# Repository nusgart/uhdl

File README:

MIT CADR HDL --- Verilog FPGA implementation of the MIT CADR

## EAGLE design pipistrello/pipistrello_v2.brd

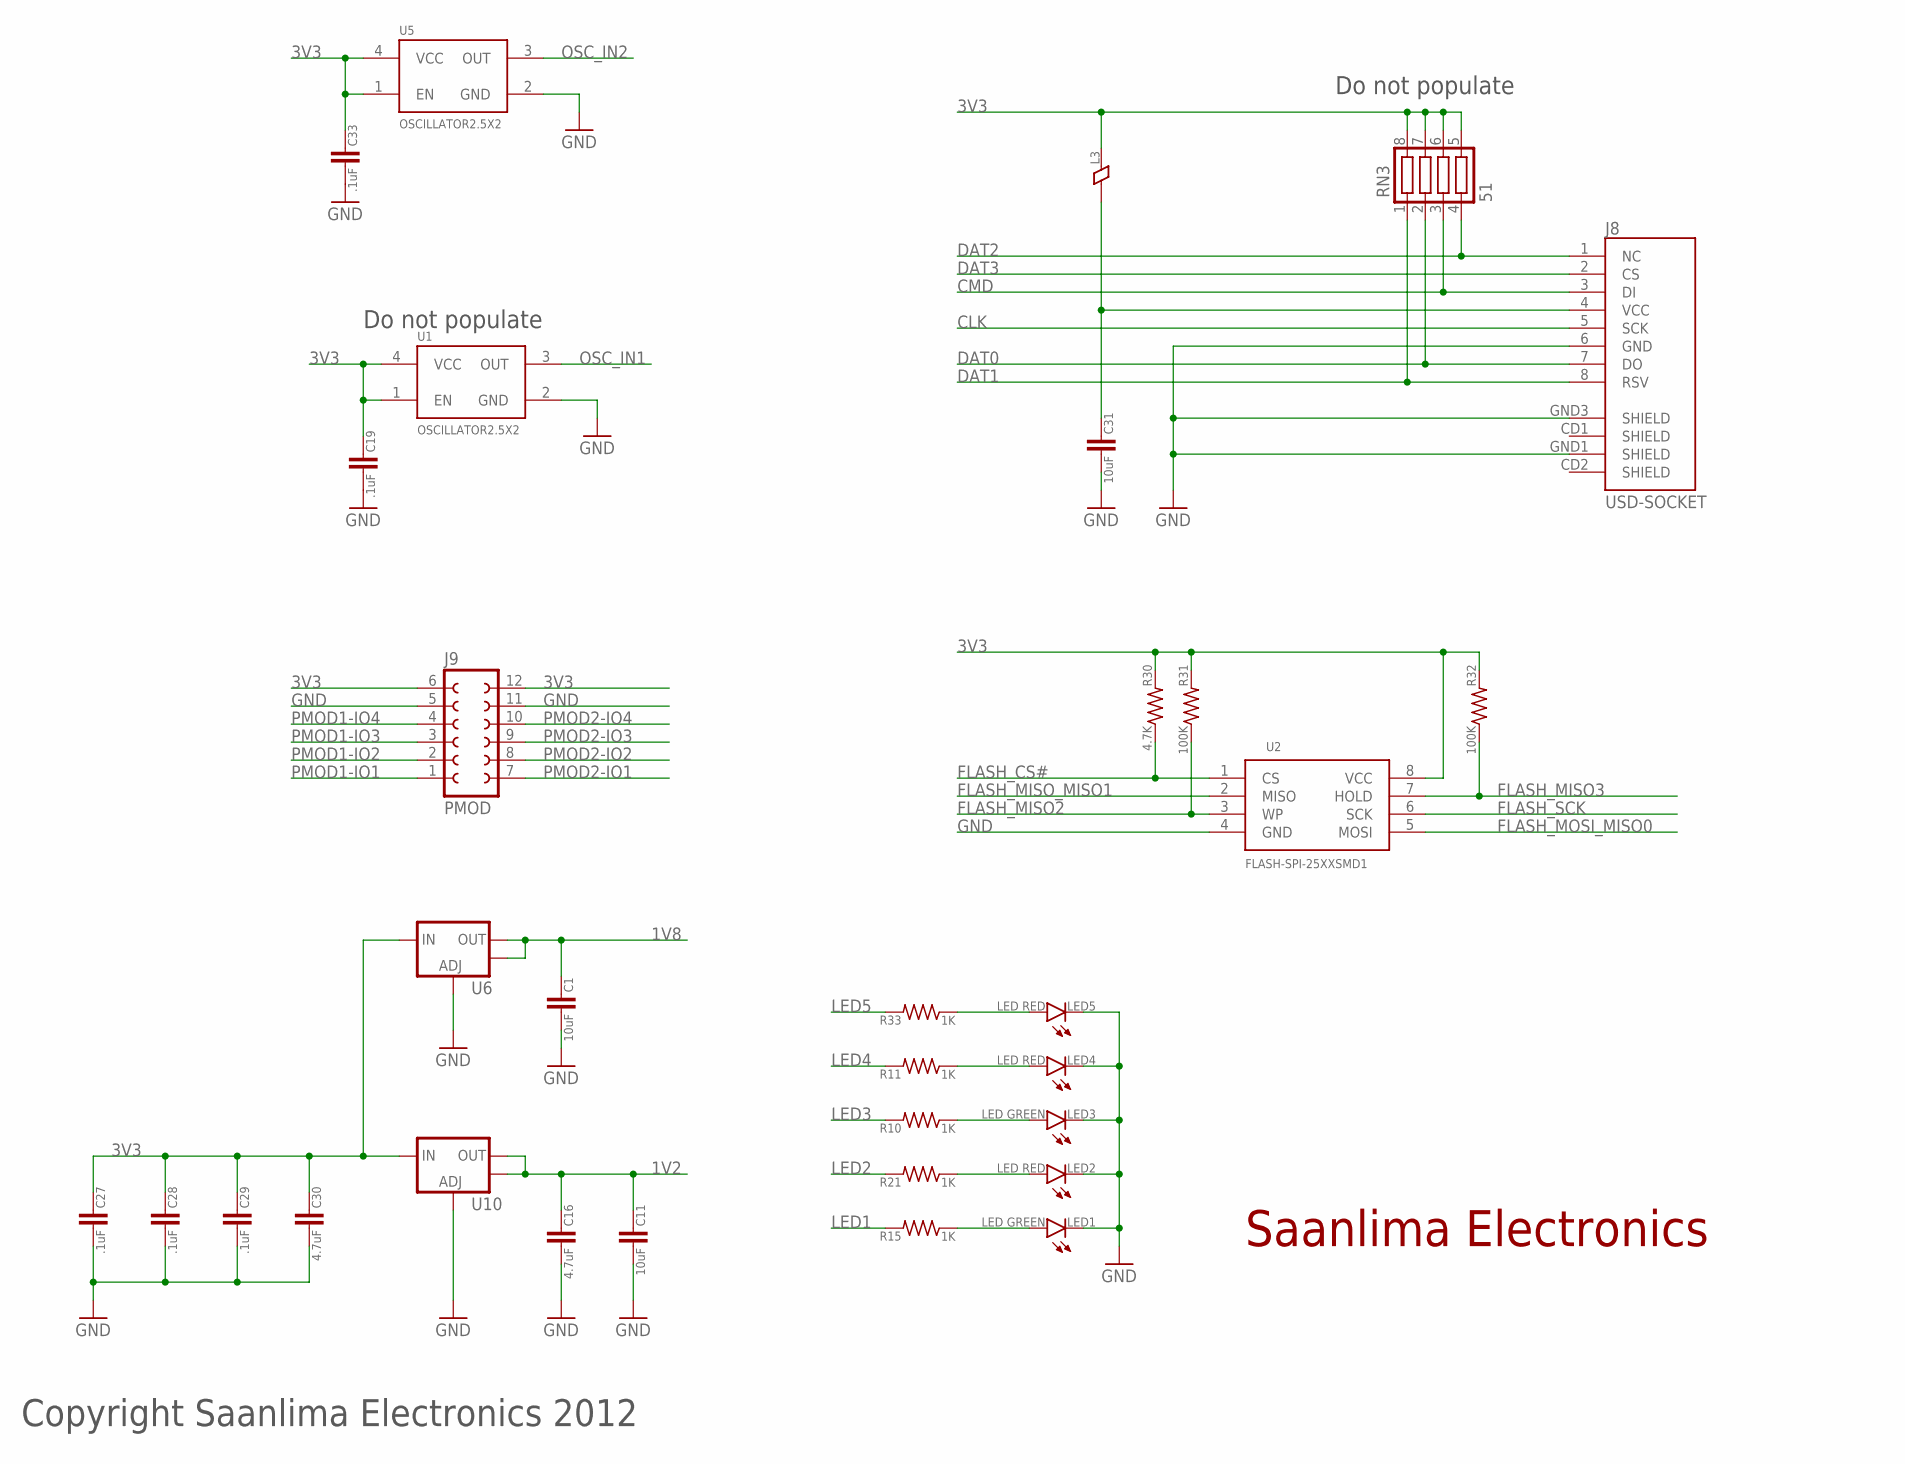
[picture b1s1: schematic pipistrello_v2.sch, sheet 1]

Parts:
C1, C11: 10uF; 0805
C16, C30: 4.7uF; 0402
C19, C27, C28, C29, C33: .1uF; 0402
C31: 10uF; 0603
J8: USD-SOCKET; MICRO-SD-SOCKET-PP
J9: PMOD
L3: FERRITE0402; 0402
LED1, LED3: LED GREEN; 0805_POL
LED2, LED4, LED5: LED RED; 0805_POL
R10, R11, R15, R21, R33: 1K; 0402
R30: 4.7K; 0402
R31, R32: 100K; 0402
RN3: 51; CTS742C083
U1, U5: OSCILLATOR2.5X2; CRYSTAL-OSC-SMD-2.5X2
U2: FLASH-SPI-25XXSMD1; SO08-EIAJ
U6, U10: V_REG_LM1117SOT223; SOT223

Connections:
1V2: C11.1, C16.1, U10.2 (OUT), U10.4 (OUT); also elsewhere on the board
1V8: C1.1, U6.2 (OUT), U6.4 (OUT); also elsewhere on the board
3V3: C19.1, C27.1, C28.1, C29.1, C30.1, C33.1, J9.6, J9.12, L3.2, R30.2, R31.2, R32.2, RN3.5, RN3.6, RN3.7, RN3.8, U1.1 (EN), U1.4 (VCC), U2.8 (VCC), U5.1 (EN), U5.4 (VCC), U6.3 (IN), U10.3 (IN); also elsewhere on the board
CLK: J8.5 (SCK); also elsewhere on the board
CMD: J8.3 (DI), RN3.3; also elsewhere on the board
DAT0: J8.7 (DO), RN3.2; also elsewhere on the board
DAT1: J8.8 (RSV), RN3.1; also elsewhere on the board
DAT2: J8.1 (NC), RN3.4; also elsewhere on the board
DAT3: J8.2 (CS); also elsewhere on the board
FLASH_CS#: R30.1, U2.1 (CS); also elsewhere on the board
FLASH_MISO2: R31.1, U2.3 (WP); also elsewhere on the board
FLASH_MISO3: R32.1, U2.7 (HOLD); also elsewhere on the board
FLASH_MISO_MISO1: U2.2 (MISO); also elsewhere on the board
FLASH_MOSI_MISO0: U2.5 (MOSI); also elsewhere on the board
FLASH_SCK: U2.6 (SCK); also elsewhere on the board
GND: C1.2, C11.2, C16.2, C19.2, C27.2, C28.2, C29.2, C30.2, C31.2, C33.2, J8.6 (GND), J8.GND1 (SHIELD), J8.GND3 (SHIELD), J9.5, J9.11, LED1.- (C), LED2.- (C), LED3.- (C), LED4.- (C), LED5.- (C), U1.2 (GND), U2.4 (GND), U5.2 (GND), U6.1 (ADJ), U10.1 (ADJ); also elsewhere on the board
LED1: R15.2; also elsewhere on the board
LED2: R21.2; also elsewhere on the board
LED3: R10.2; also elsewhere on the board
LED4: R11.2; also elsewhere on the board
LED5: R33.2; also elsewhere on the board
unnamed: LED2.+ (A), R21.1
unnamed: LED3.+ (A), R10.1
unnamed: C31.1, J8.4 (VCC), L3.1
unnamed: LED1.+ (A), R15.1
unnamed: LED4.+ (A), R11.1
unnamed: LED5.+ (A), R33.1
OSC_IN1: U1.3 (OUT); also elsewhere on the board
OSC_IN2: U5.3 (OUT); also elsewhere on the board
PMOD1-IO1: J9.1; also elsewhere on the board
PMOD1-IO2: J9.2; also elsewhere on the board
PMOD1-IO3: J9.3; also elsewhere on the board
PMOD1-IO4: J9.4; also elsewhere on the board
PMOD2-IO1: J9.7; also elsewhere on the board
PMOD2-IO2: J9.8; also elsewhere on the board
PMOD2-IO3: J9.9; also elsewhere on the board
PMOD2-IO4: J9.10; also elsewhere on the board

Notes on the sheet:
Saanlima Electronics
Copyright Saanlima Electronics 2012
Do not populate

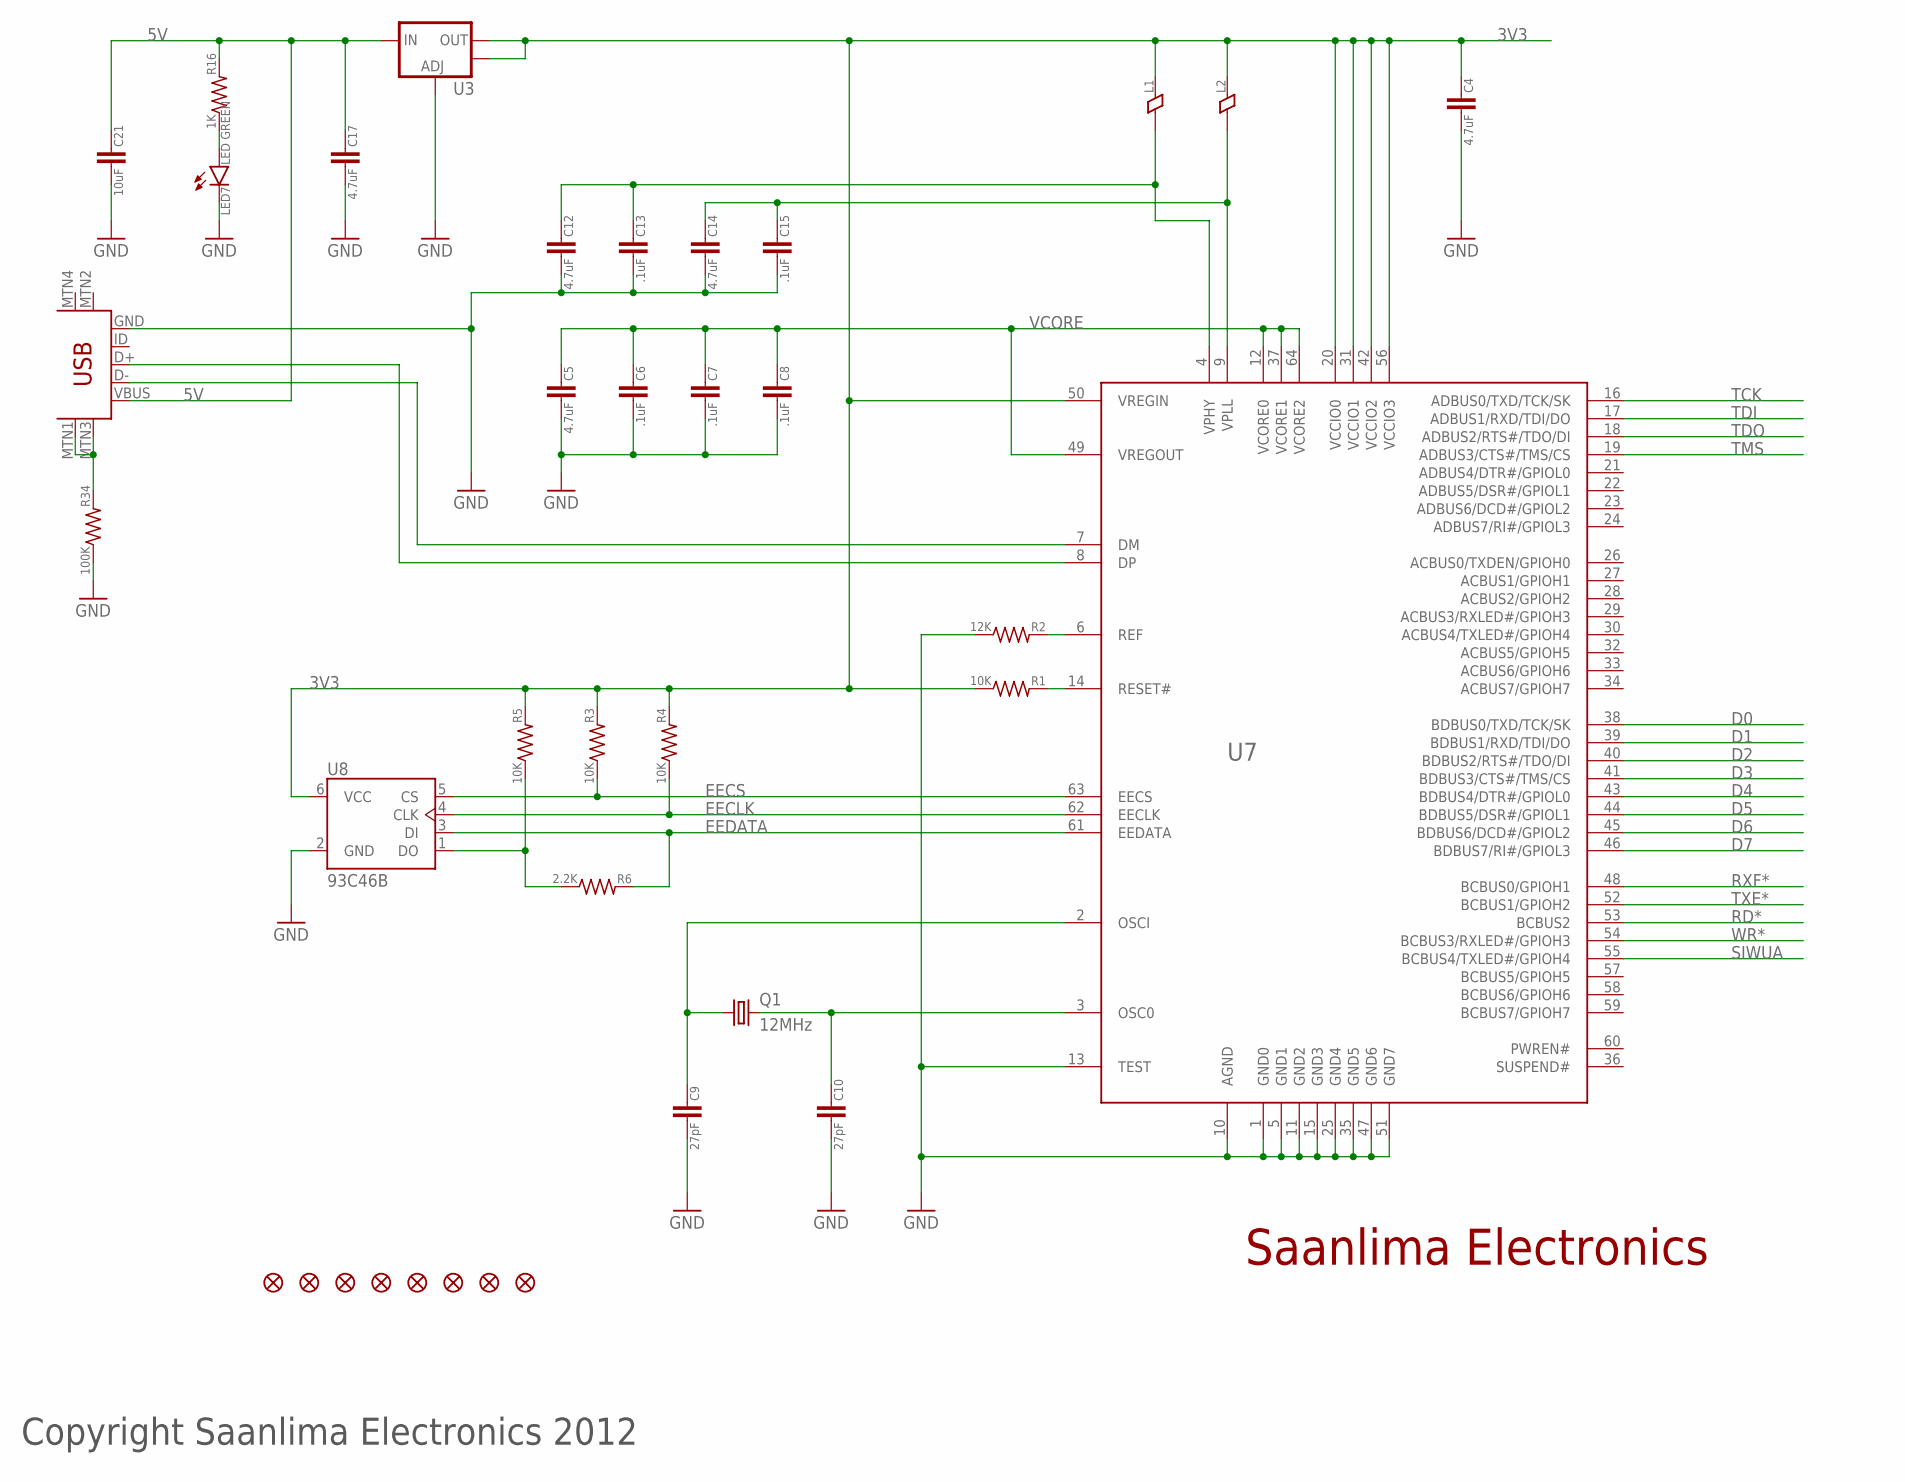
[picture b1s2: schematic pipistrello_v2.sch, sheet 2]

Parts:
C4, C5, C12, C14, C17: 4.7uF; 0402
C6, C7, C8, C13, C15: .1uF; 0402
C9, C10: 27pF; 0402
C21: 10uF; 0603
J7: USB-MINIB-5PIN; USB-MINIB
JP1, JP2, JP3, JP4, JP5, JP6, JP7, JP8: FIDUCIAL1X2; FIDUCIAL-1X2
L1, L2: FERRITE0402; 0402
LED7: LED GREEN; 0805_POL
Q1: 12MHz; CRYSTAL3.2X2.5MM
R1, R3, R4, R5: 10K; 0402
R2: 12K; 0402
R6: 2.2K; 0402
R16: 1K; 0402
R34: 100K; 0402
U3: V_REG_LM1117SOT223; SOT223
U7: FT2232H; LQFP64
U8: 93C46B; SOT23-6

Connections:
3V3: C4.1, L1.2, L2.2, R1.1, R3.2, R4.2, R5.2, U3.2 (OUT), U3.4 (OUT), U7.20 (VCCIO0), U7.31 (VCCIO1), U7.42 (VCCIO2), U7.50 (VREGIN), U7.56 (VCCIO3), U8.6 (VCC); also elsewhere on the board
5V: C17.1, C21.1, J7.VBUS, R16.2, U3.3 (IN); also elsewhere on the board
D0: U7.38 (BDBUS0/TXD/TCK/SK); also elsewhere on the board
D1: U7.39 (BDBUS1/RXD/TDI/DO); also elsewhere on the board
D2: U7.40 (BDBUS2/RTS#/TDO/DI); also elsewhere on the board
D3: U7.41 (BDBUS3/CTS#/TMS/CS); also elsewhere on the board
D4: U7.43 (BDBUS4/DTR#/GPIOL0); also elsewhere on the board
D5: U7.44 (BDBUS5/DSR#/GPIOL1); also elsewhere on the board
D6: U7.45 (BDBUS6/DCD#/GPIOL2); also elsewhere on the board
D7: U7.46 (BDBUS7/RI#/GPIOL3); also elsewhere on the board
EECLK: R4.1, U7.62 (EECLK), U8.4 (CLK)
EECS: R3.1, U7.63 (EECS), U8.5 (CS)
EEDATA: R6.2, U7.61 (EEDATA), U8.3 (DI)
GND: C4.2, C5.2, C6.2, C7.2, C8.2, C9.2, C10.2, C12.2, C13.2, C14.2, C15.2, C17.2, C21.2, J7.GND, LED7.- (C), R2.1, R34.1, U3.1 (ADJ), U7.1 (GND0), U7.5 (GND1), U7.10 (AGND), U7.11 (GND2), U7.13 (TEST), U7.15 (GND3), U7.25 (GND4), U7.35 (GND5), U7.47 (GND6), U7.51 (GND7), U8.2 (GND); also elsewhere on the board
unnamed: J7.MTN1 (MTN2), J7.MTN3 (MTN1), R34.2
unnamed: C9.1, Q1.1, U7.2 (OSCI)
unnamed: C10.1, Q1.3 (2), U7.3 (OSC0)
unnamed: LED7.+ (A), R16.1
unnamed: J7.D-, U7.7 (DM)
unnamed: J7.D+, U7.8 (DP)
unnamed: C14.1, C15.1, L2.1, U7.9 (VPLL)
unnamed: R1.2, U7.14 (RESET#)
unnamed: R2.2, U7.6 (REF)
unnamed: C12.1, C13.1, L1.1, U7.4 (VPHY)
unnamed: R5.1, R6.1, U8.1 (DO)
RD*: U7.53 (BCBUS2); also elsewhere on the board
RXF*: U7.48 (BCBUS0/GPIOH1); also elsewhere on the board
SIWUA: U7.55 (BCBUS4/TXLED#/GPIOH4); also elsewhere on the board
TCK: U7.16 (ADBUS0/TXD/TCK/SK); also elsewhere on the board
TDI: U7.17 (ADBUS1/RXD/TDI/DO); also elsewhere on the board
TDO: U7.18 (ADBUS2/RTS#/TDO/DI); also elsewhere on the board
TMS: U7.19 (ADBUS3/CTS#/TMS/CS); also elsewhere on the board
TXE*: U7.52 (BCBUS1/GPIOH2); also elsewhere on the board
VCORE: C5.1, C6.1, C7.1, C8.1, U7.12 (VCORE0), U7.37 (VCORE1), U7.49 (VREGOUT), U7.64 (VCORE2)
WR*: U7.54 (BCBUS3/RXLED#/GPIOH3); also elsewhere on the board

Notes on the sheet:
Saanlima Electronics
Copyright Saanlima Electronics 2012

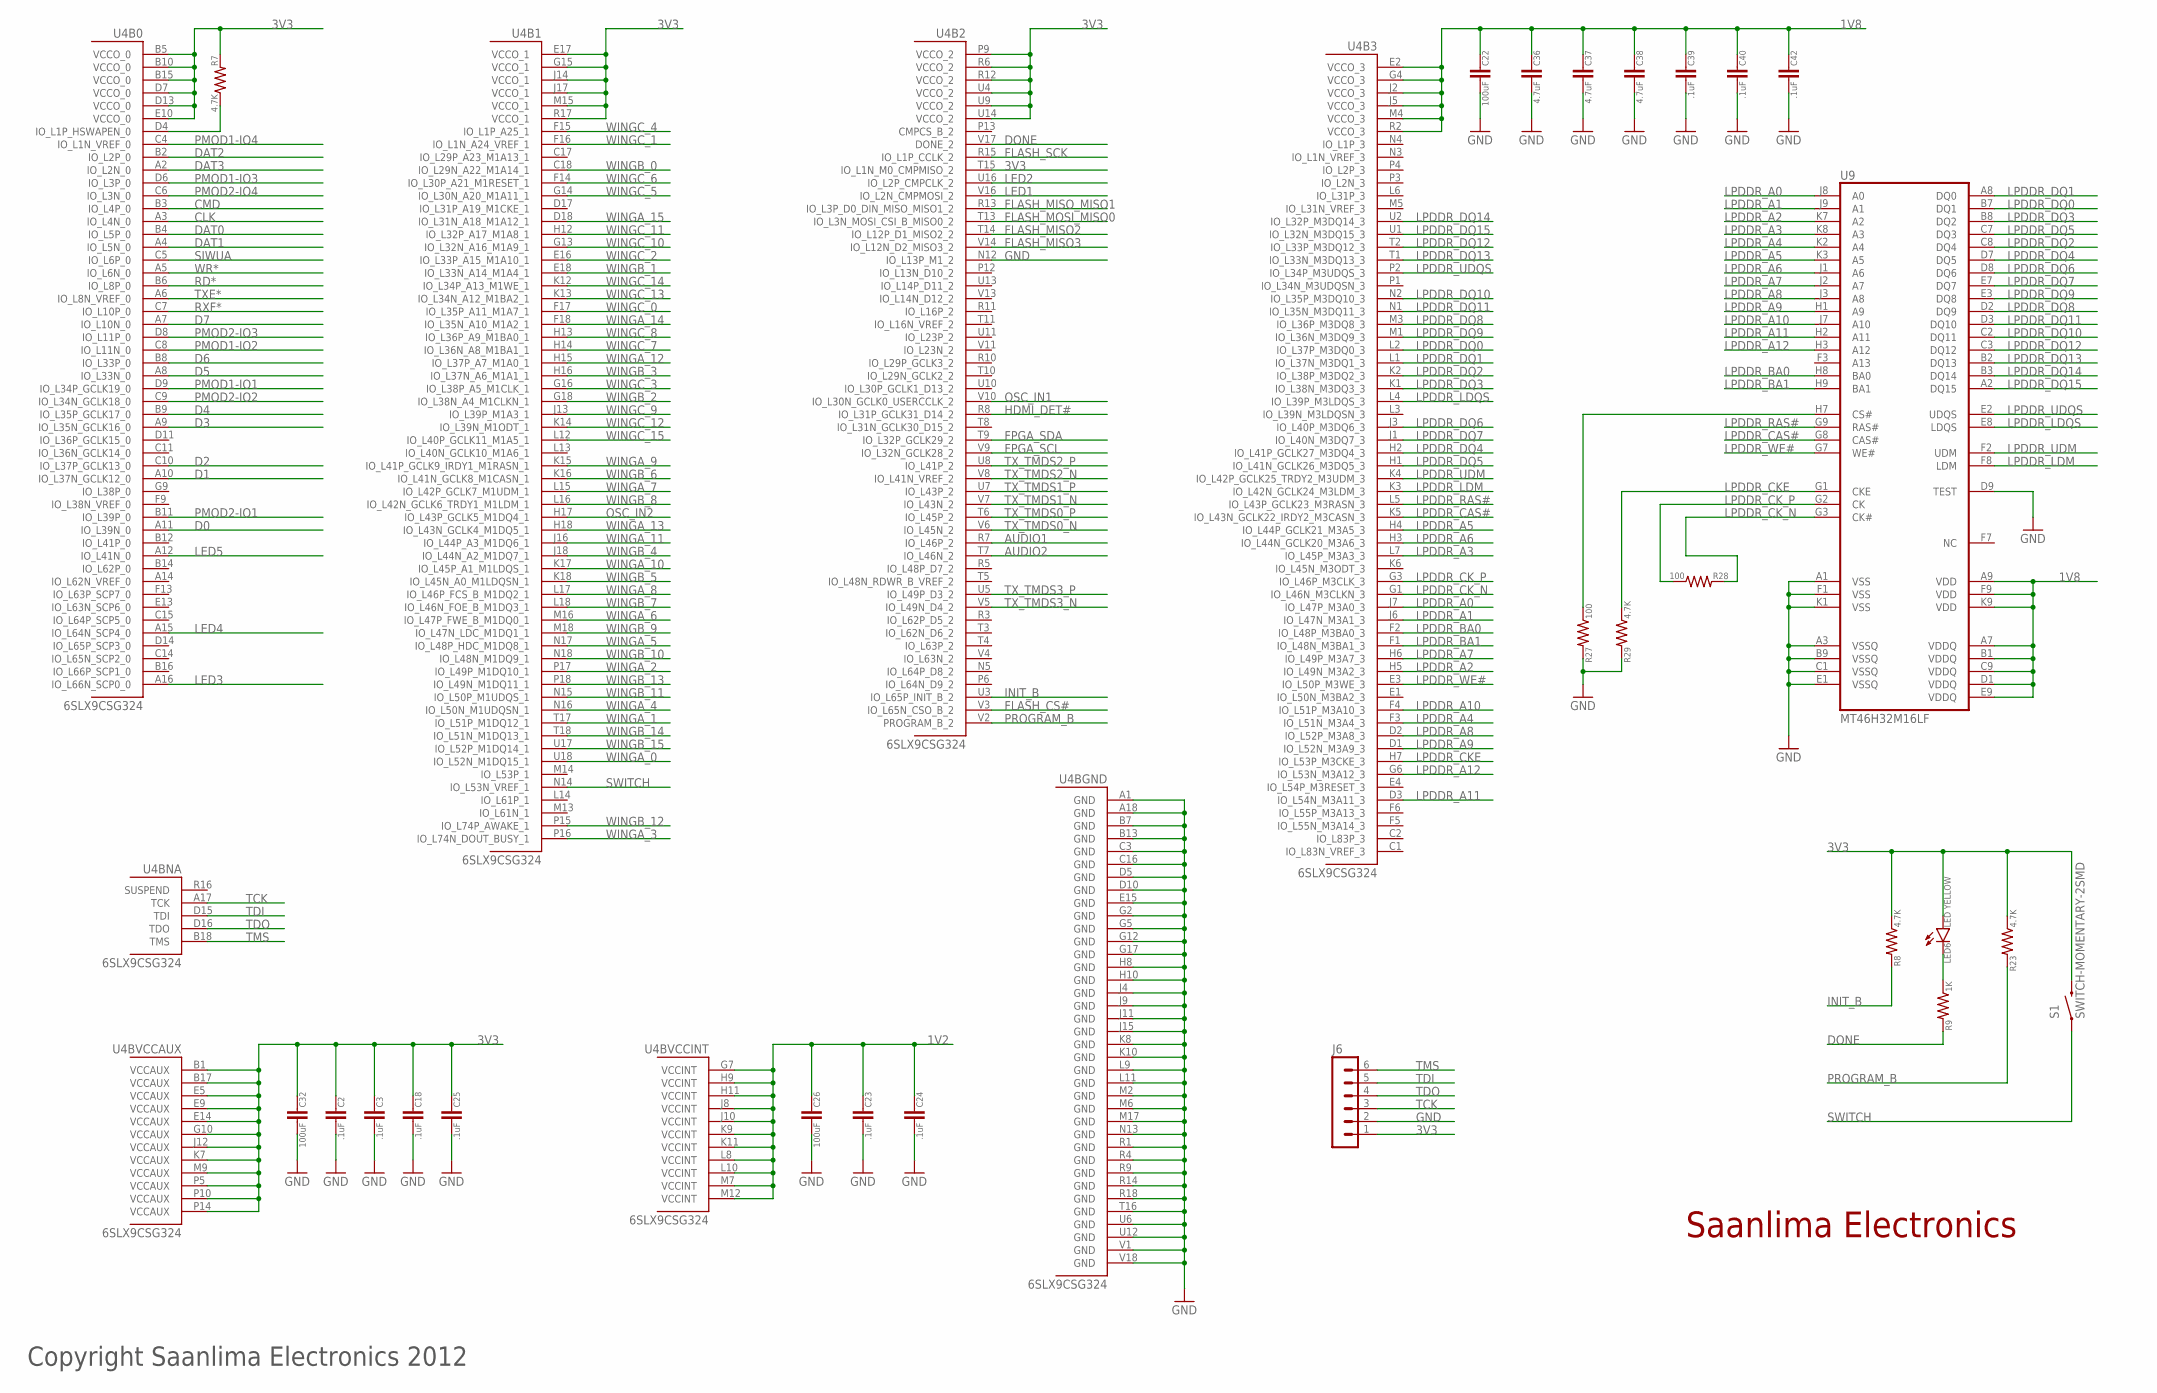
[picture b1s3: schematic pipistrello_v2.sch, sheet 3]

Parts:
C2, C3, C18, C23, C24, C25, C39, C40, C42: .1uF; 0402
C22, C26, C32: 100uF; 1206
C36, C37, C38: 4.7uF; 0402
J6: MA06-1
LED6: LED YELLOW; 0805_POL
R7, R8, R23, R29: 4.7K; 0402
R9: 1K; 0402
R27, R28: 100; 0402
S1: SWITCH-MOMENTARY-2SMD; TACTILE_SWITCH_SMD
U4: 6SLX9CSG324; CS324
U9: MT46H32M16LF; FBFA60-6X10

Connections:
1V2: C23.1, C24.1, C26.1, U4.G7 (VCCINT), U4.H9 (VCCINT), U4.H11 (VCCINT), U4.J8 (VCCINT), U4.J10 (VCCINT), U4.K9 (VCCINT), U4.K11 (VCCINT), U4.L8 (VCCINT), U4.L10 (VCCINT), U4.M7 (VCCINT), U4.M12 (VCCINT); also elsewhere on the board
1V8: C22.1, C36.1, C37.1, C38.1, C39.1, C40.1, C42.1, U4.E2 (VCCO_3), U4.G4 (VCCO_3), U4.J2 (VCCO_3), U4.J5 (VCCO_3), U4.M4 (VCCO_3), U4.R2 (VCCO_3), U9.A7 (VDDQ), U9.A9 (VDD), U9.B1 (VDDQ), U9.C9 (VDDQ), U9.D1 (VDDQ), U9.E9 (VDDQ), U9.F9 (VDD), U9.K9 (VDD); also elsewhere on the board
3V3: C2.1, C3.1, C18.1, C25.1, C32.1, J6.1, LED6.+ (A), R7.2, R8.1, R23.1, S1.3 (2), U4.B1 (VCCAUX), U4.B5 (VCCO_0), U4.B10 (VCCO_0), U4.B15 (VCCO_0), U4.B17 (VCCAUX), U4.D7 (VCCO_0), U4.D13 (VCCO_0), U4.E5 (VCCAUX), U4.E9 (VCCAUX), U4.E10 (VCCO_0), U4.E14 (VCCAUX), U4.E17 (VCCO_1), U4.G10 (VCCAUX), U4.G15 (VCCO_1), U4.J12 (VCCAUX), U4.J14 (VCCO_1), U4.J17 (VCCO_1), U4.K7 (VCCAUX), U4.M9 (VCCAUX), U4.M15 (VCCO_1), U4.P5 (VCCAUX), U4.P9 (VCCO_2), U4.P10 (VCCAUX), U4.P14 (VCCAUX), U4.R6 (VCCO_2), U4.R12 (VCCO_2), U4.R17 (VCCO_1), U4.T15 (IO_L1N_M0_CMPMISO_2), U4.U4 (VCCO_2), U4.U9 (VCCO_2), U4.U14 (VCCO_2); also elsewhere on the board
AUDIO1: U4.R7 (IO_L46P_2); also elsewhere on the board
AUDIO2: U4.T7 (IO_L46N_2); also elsewhere on the board
CLK: U4.A3 (IO_L4N_0); also elsewhere on the board
CMD: U4.B3 (IO_L4P_0); also elsewhere on the board
D0: U4.A11 (IO_L39N_0); also elsewhere on the board
D1: U4.A10 (IO_L37N_GCLK12_0); also elsewhere on the board
D2: U4.C10 (IO_L37P_GCLK13_0); also elsewhere on the board
D3: U4.A9 (IO_L35N_GCLK16_0); also elsewhere on the board
D4: U4.B9 (IO_L35P_GCLK17_0); also elsewhere on the board
D5: U4.A8 (IO_L33N_0); also elsewhere on the board
D6: U4.B8 (IO_L33P_0); also elsewhere on the board
D7: U4.A7 (IO_L10N_0); also elsewhere on the board
DAT0: U4.B4 (IO_L5P_0); also elsewhere on the board
DAT1: U4.A4 (IO_L5N_0); also elsewhere on the board
DAT2: U4.B2 (IO_L2P_0); also elsewhere on the board
DAT3: U4.A2 (IO_L2N_0); also elsewhere on the board
DONE: R9.2, U4.V17 (DONE_2)
FLASH_CS#: U4.V3 (IO_L65N_CSO_B_2); also elsewhere on the board
FLASH_MISO2: U4.T14 (IO_L12P_D1_MISO2_2); also elsewhere on the board
FLASH_MISO3: U4.V14 (IO_L12N_D2_MISO3_2); also elsewhere on the board
FLASH_MISO_MISO1: U4.R13 (IO_L3P_D0_DIN_MISO_MISO1_2); also elsewhere on the board
FLASH_MOSI_MISO0: U4.T13 (IO_L3N_MOSI_CSI_B_MISO0_2); also elsewhere on the board
FLASH_SCK: U4.R15 (IO_L1P_CCLK_2); also elsewhere on the board
FPGA_SCL: U4.V9 (IO_L32N_GCLK28_2); also elsewhere on the board
FPGA_SDA: U4.T9 (IO_L32P_GCLK29_2); also elsewhere on the board
GND: C2.2, C3.2, C18.2, C22.2, C23.2, C24.2, C25.2, C26.2, C32.2, C36.2, C37.2, C38.2, C39.2, C40.2, C42.2, J6.2, R27.2, R29.2, U4.A1 (GND), U4.A18 (GND), U4.B7 (GND), U4.B13 (GND), U4.C3 (GND), U4.C16 (GND), U4.D5 (GND), U4.D10 (GND), U4.E15 (GND), U4.G2 (GND), U4.G5 (GND), U4.G12 (GND), U4.G17 (GND), U4.H8 (GND), U4.H10 (GND), U4.J4 (GND), U4.J9 (GND), U4.J11 (GND), U4.J15 (GND), U4.K8 (GND), U4.K10 (GND), U4.L9 (GND), U4.L11 (GND), U4.M2 (GND), U4.M6 (GND), U4.M17 (GND), U4.N12 (IO_L13P_M1_2), U4.N13 (GND), U4.R1 (GND), U4.R4 (GND), U4.R9 (GND), U4.R14 (GND), U4.R18 (GND), U4.T16 (GND), U4.U6 (GND), U4.U12 (GND), U4.V1 (GND), U4.V18 (GND), U9.A1 (VSS), U9.A3 (VSSQ), U9.B9 (VSSQ), U9.C1 (VSSQ), U9.D9 (TEST), U9.E1 (VSSQ), U9.F1 (VSS), U9.K1 (VSS); also elsewhere on the board
HDMI_DET#: U4.R8 (IO_L31P_GCLK31_D14_2); also elsewhere on the board
INIT_B: R8.2, U4.U3 (IO_L65P_INIT_B_2)
LED1: U4.V16 (IO_L2N_CMPMOSI_2); also elsewhere on the board
LED2: U4.U16 (IO_L2P_CMPCLK_2); also elsewhere on the board
LED3: U4.A16 (IO_L66N_SCP0_0); also elsewhere on the board
LED4: U4.A15 (IO_L64N_SCP4_0); also elsewhere on the board
LED5: U4.A12 (IO_L41N_0); also elsewhere on the board
LPDDR_A0: U4.J7 (IO_L47P_M3A0_3), U9.J8 (A0)
LPDDR_A1: U4.J6 (IO_L47N_M3A1_3), U9.J9 (A1)
LPDDR_A2: U4.H5 (IO_L49N_M3A2_3), U9.K7 (A2)
LPDDR_A3: U4.L7 (IO_L45P_M3A3_3), U9.K8 (A3)
LPDDR_A4: U4.F3 (IO_L51N_M3A4_3), U9.K2 (A4)
LPDDR_A5: U4.H4 (IO_L44P_GCLK21_M3A5_3), U9.K3 (A5)
LPDDR_A6: U4.H3 (IO_L44N_GCLK20_M3A6_3), U9.J1 (A6)
LPDDR_A7: U4.H6 (IO_L49P_M3A7_3), U9.J2 (A7)
LPDDR_A8: U4.D2 (IO_L52P_M3A8_3), U9.J3 (A8)
LPDDR_A9: U4.D1 (IO_L52N_M3A9_3), U9.H1 (A9)
LPDDR_A10: U4.F4 (IO_L51P_M3A10_3), U9.J7 (A10)
LPDDR_A11: U4.D3 (IO_L54N_M3A11_3), U9.H2 (A11)
LPDDR_A12: U4.G6 (IO_L53N_M3A12_3), U9.H3 (A12)
LPDDR_BA0: U4.F2 (IO_L48P_M3BA0_3), U9.H8 (BA0)
LPDDR_BA1: U4.F1 (IO_L48N_M3BA1_3), U9.H9 (BA1)
LPDDR_CAS#: U4.K5 (IO_L43N_GCLK22_IRDY2_M3CASN_3), U9.G8 (CAS#)
LPDDR_CKE: R29.1, U4.H7 (IO_L53P_M3CKE_3), U9.G1 (CKE)
LPDDR_CK_N: R28.2, U4.G1 (IO_L46N_M3CLKN_3), U9.G3 (CK#)
LPDDR_CK_P: R28.1, U4.G3 (IO_L46P_M3CLK_3), U9.G2 (CK)
LPDDR_CS#: R27.1, U9.H7 (CS#)
LPDDR_DQ0: U4.L2 (IO_L37P_M3DQ0_3), U9.B7 (DQ1)
LPDDR_DQ1: U4.L1 (IO_L37N_M3DQ1_3), U9.A8 (DQ0)
LPDDR_DQ2: U4.K2 (IO_L38P_M3DQ2_3), U9.C8 (DQ4)
LPDDR_DQ3: U4.K1 (IO_L38N_M3DQ3_3), U9.B8 (DQ2)
LPDDR_DQ4: U4.H2 (IO_L41P_GCLK27_M3DQ4_3), U9.D7 (DQ5)
LPDDR_DQ5: U4.H1 (IO_L41N_GCLK26_M3DQ5_3), U9.C7 (DQ3)
LPDDR_DQ6: U4.J3 (IO_L40P_M3DQ6_3), U9.D8 (DQ6)
LPDDR_DQ7: U4.J1 (IO_L40N_M3DQ7_3), U9.E7 (DQ7)
LPDDR_DQ8: U4.M3 (IO_L36P_M3DQ8_3), U9.D2 (DQ9)
LPDDR_DQ9: U4.M1 (IO_L36N_M3DQ9_3), U9.E3 (DQ8)
LPDDR_DQ10: U4.N2 (IO_L35P_M3DQ10_3), U9.C2 (DQ11)
LPDDR_DQ11: U4.N1 (IO_L35N_M3DQ11_3), U9.D3 (DQ10)
LPDDR_DQ12: U4.T2 (IO_L33P_M3DQ12_3), U9.C3 (DQ12)
LPDDR_DQ13: U4.T1 (IO_L33N_M3DQ13_3), U9.B2 (DQ13)
LPDDR_DQ14: U4.U2 (IO_L32P_M3DQ14_3), U9.B3 (DQ14)
LPDDR_DQ15: U4.U1 (IO_L32N_M3DQ15_3), U9.A2 (DQ15)
LPDDR_LDM: U4.K3 (IO_L42N_GCLK24_M3LDM_3), U9.F8 (LDM)
LPDDR_LDQS: U4.L4 (IO_L39P_M3LDQS_3), U9.E8 (LDQS)
LPDDR_RAS#: U4.L5 (IO_L43P_GCLK23_M3RASN_3), U9.G9 (RAS#)
LPDDR_UDM: U4.K4 (IO_L42P_GCLK25_TRDY2_M3UDM_3), U9.F2 (UDM)
LPDDR_UDQS: U4.P2 (IO_L34P_M3UDQS_3), U9.E2 (UDQS)
LPDDR_WE#: U4.E3 (IO_L50P_M3WE_3), U9.G7 (WE#)
unnamed: R7.1, U4.D4 (IO_L1P_HSWAPEN_0)
unnamed: LED6.- (C), R9.1
OSC_IN1: U4.V10 (IO_L30N_GCLK0_USERCCLK_2); also elsewhere on the board
OSC_IN2: U4.H17 (IO_L43P_GCLK5_M1DQ4_1); also elsewhere on the board
PMOD1-IO1: U4.D9 (IO_L34P_GCLK19_0); also elsewhere on the board
PMOD1-IO2: U4.C8 (IO_L11N_0); also elsewhere on the board
PMOD1-IO3: U4.D6 (IO_L3P_0); also elsewhere on the board
PMOD1-IO4: U4.C4 (IO_L1N_VREF_0); also elsewhere on the board
PMOD2-IO1: U4.B11 (IO_L39P_0); also elsewhere on the board
PMOD2-IO2: U4.C9 (IO_L34N_GCLK18_0); also elsewhere on the board
PMOD2-IO3: U4.D8 (IO_L11P_0); also elsewhere on the board
PMOD2-IO4: U4.C6 (IO_L3N_0); also elsewhere on the board
PROGRAM_B: R23.2, U4.V2 (PROGRAM_B_2)
RD*: U4.B6 (IO_L8P_0); also elsewhere on the board
RXF*: U4.C7 (IO_L10P_0); also elsewhere on the board
SIWUA: U4.C5 (IO_L6P_0); also elsewhere on the board
SWITCH: S1.1, U4.N14 (IO_L53N_VREF_1)
TCK: J6.3, U4.A17 (TCK); also elsewhere on the board
TDI: J6.5, U4.D15 (TDI); also elsewhere on the board
TDO: J6.4, U4.D16 (TDO); also elsewhere on the board
TMS: J6.6, U4.B18 (TMS); also elsewhere on the board
TXE*: U4.A6 (IO_L8N_VREF_0); also elsewhere on the board
TX_TMDS0_N: U4.V6 (IO_L45N_2); also elsewhere on the board
TX_TMDS0_P: U4.T6 (IO_L45P_2); also elsewhere on the board
TX_TMDS1_N: U4.V7 (IO_L43N_2); also elsewhere on the board
TX_TMDS1_P: U4.U7 (IO_L43P_2); also elsewhere on the board
TX_TMDS2_N: U4.V8 (IO_L41N_VREF_2); also elsewhere on the board
TX_TMDS2_P: U4.U8 (IO_L41P_2); also elsewhere on the board
TX_TMDS3_N: U4.V5 (IO_L49N_D4_2); also elsewhere on the board
TX_TMDS3_P: U4.U5 (IO_L49P_D3_2); also elsewhere on the board
WINGA_0: U4.U18 (IO_L52N_M1DQ15_1); also elsewhere on the board
WINGA_1: U4.T17 (IO_L51P_M1DQ12_1); also elsewhere on the board
WINGA_2: U4.P17 (IO_L49P_M1DQ10_1); also elsewhere on the board
WINGA_3: U4.P16 (IO_L74N_DOUT_BUSY_1); also elsewhere on the board
WINGA_4: U4.N16 (IO_L50N_M1UDQSN_1); also elsewhere on the board
WINGA_5: U4.N17 (IO_L48P_HDC_M1DQ8_1); also elsewhere on the board
WINGA_6: U4.M16 (IO_L47P_FWE_B_M1DQ0_1); also elsewhere on the board
WINGA_7: U4.L15 (IO_L42P_GCLK7_M1UDM_1); also elsewhere on the board
WINGA_8: U4.L17 (IO_L46P_FCS_B_M1DQ2_1); also elsewhere on the board
WINGA_9: U4.K15 (IO_L41P_GCLK9_IRDY1_M1RASN_1); also elsewhere on the board
WINGA_10: U4.K17 (IO_L45P_A1_M1LDQS_1); also elsewhere on the board
WINGA_11: U4.J16 (IO_L44P_A3_M1DQ6_1); also elsewhere on the board
WINGA_12: U4.H15 (IO_L37P_A7_M1A0_1); also elsewhere on the board
WINGA_13: U4.H18 (IO_L43N_GCLK4_M1DQ5_1); also elsewhere on the board
WINGA_14: U4.F18 (IO_L35N_A10_M1A2_1); also elsewhere on the board
WINGA_15: U4.D18 (IO_L31N_A18_M1A12_1); also elsewhere on the board
WINGB_0: U4.C18 (IO_L29N_A22_M1A14_1); also elsewhere on the board
WINGB_1: U4.E18 (IO_L33N_A14_M1A4_1); also elsewhere on the board
WINGB_2: U4.G18 (IO_L38N_A4_M1CLKN_1); also elsewhere on the board
WINGB_3: U4.H16 (IO_L37N_A6_M1A1_1); also elsewhere on the board
WINGB_4: U4.J18 (IO_L44N_A2_M1DQ7_1); also elsewhere on the board
WINGB_5: U4.K18 (IO_L45N_A0_M1LDQSN_1); also elsewhere on the board
WINGB_6: U4.K16 (IO_L41N_GCLK8_M1CASN_1); also elsewhere on the board
WINGB_7: U4.L18 (IO_L46N_FOE_B_M1DQ3_1); also elsewhere on the board
WINGB_8: U4.L16 (IO_L42N_GCLK6_TRDY1_M1LDM_1); also elsewhere on the board
WINGB_9: U4.M18 (IO_L47N_LDC_M1DQ1_1); also elsewhere on the board
WINGB_10: U4.N18 (IO_L48N_M1DQ9_1); also elsewhere on the board
WINGB_11: U4.N15 (IO_L50P_M1UDQS_1); also elsewhere on the board
WINGB_12: U4.P15 (IO_L74P_AWAKE_1); also elsewhere on the board
WINGB_13: U4.P18 (IO_L49N_M1DQ11_1); also elsewhere on the board
WINGB_14: U4.T18 (IO_L51N_M1DQ13_1); also elsewhere on the board
WINGB_15: U4.U17 (IO_L52P_M1DQ14_1); also elsewhere on the board
WINGC_0: U4.F17 (IO_L35P_A11_M1A7_1); also elsewhere on the board
WINGC_1: U4.F16 (IO_L1N_A24_VREF_1); also elsewhere on the board
WINGC_2: U4.E16 (IO_L33P_A15_M1A10_1); also elsewhere on the board
WINGC_3: U4.G16 (IO_L38P_A5_M1CLK_1); also elsewhere on the board
WINGC_4: U4.F15 (IO_L1P_A25_1); also elsewhere on the board
WINGC_5: U4.G14 (IO_L30N_A20_M1A11_1); also elsewhere on the board
WINGC_6: U4.F14 (IO_L30P_A21_M1RESET_1); also elsewhere on the board
WINGC_7: U4.H14 (IO_L36N_A8_M1BA1_1); also elsewhere on the board
WINGC_8: U4.H13 (IO_L36P_A9_M1BA0_1); also elsewhere on the board
WINGC_9: U4.J13 (IO_L39P_M1A3_1); also elsewhere on the board
WINGC_10: U4.G13 (IO_L32N_A16_M1A9_1); also elsewhere on the board
WINGC_11: U4.H12 (IO_L32P_A17_M1A8_1); also elsewhere on the board
WINGC_12: U4.K14 (IO_L39N_M1ODT_1); also elsewhere on the board
WINGC_13: U4.K13 (IO_L34N_A12_M1BA2_1); also elsewhere on the board
WINGC_14: U4.K12 (IO_L34P_A13_M1WE_1); also elsewhere on the board
WINGC_15: U4.L12 (IO_L40P_GCLK11_M1A5_1); also elsewhere on the board
WR*: U4.A5 (IO_L6N_0); also elsewhere on the board

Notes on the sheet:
Saanlima Electronics
Copyright Saanlima Electronics 2012

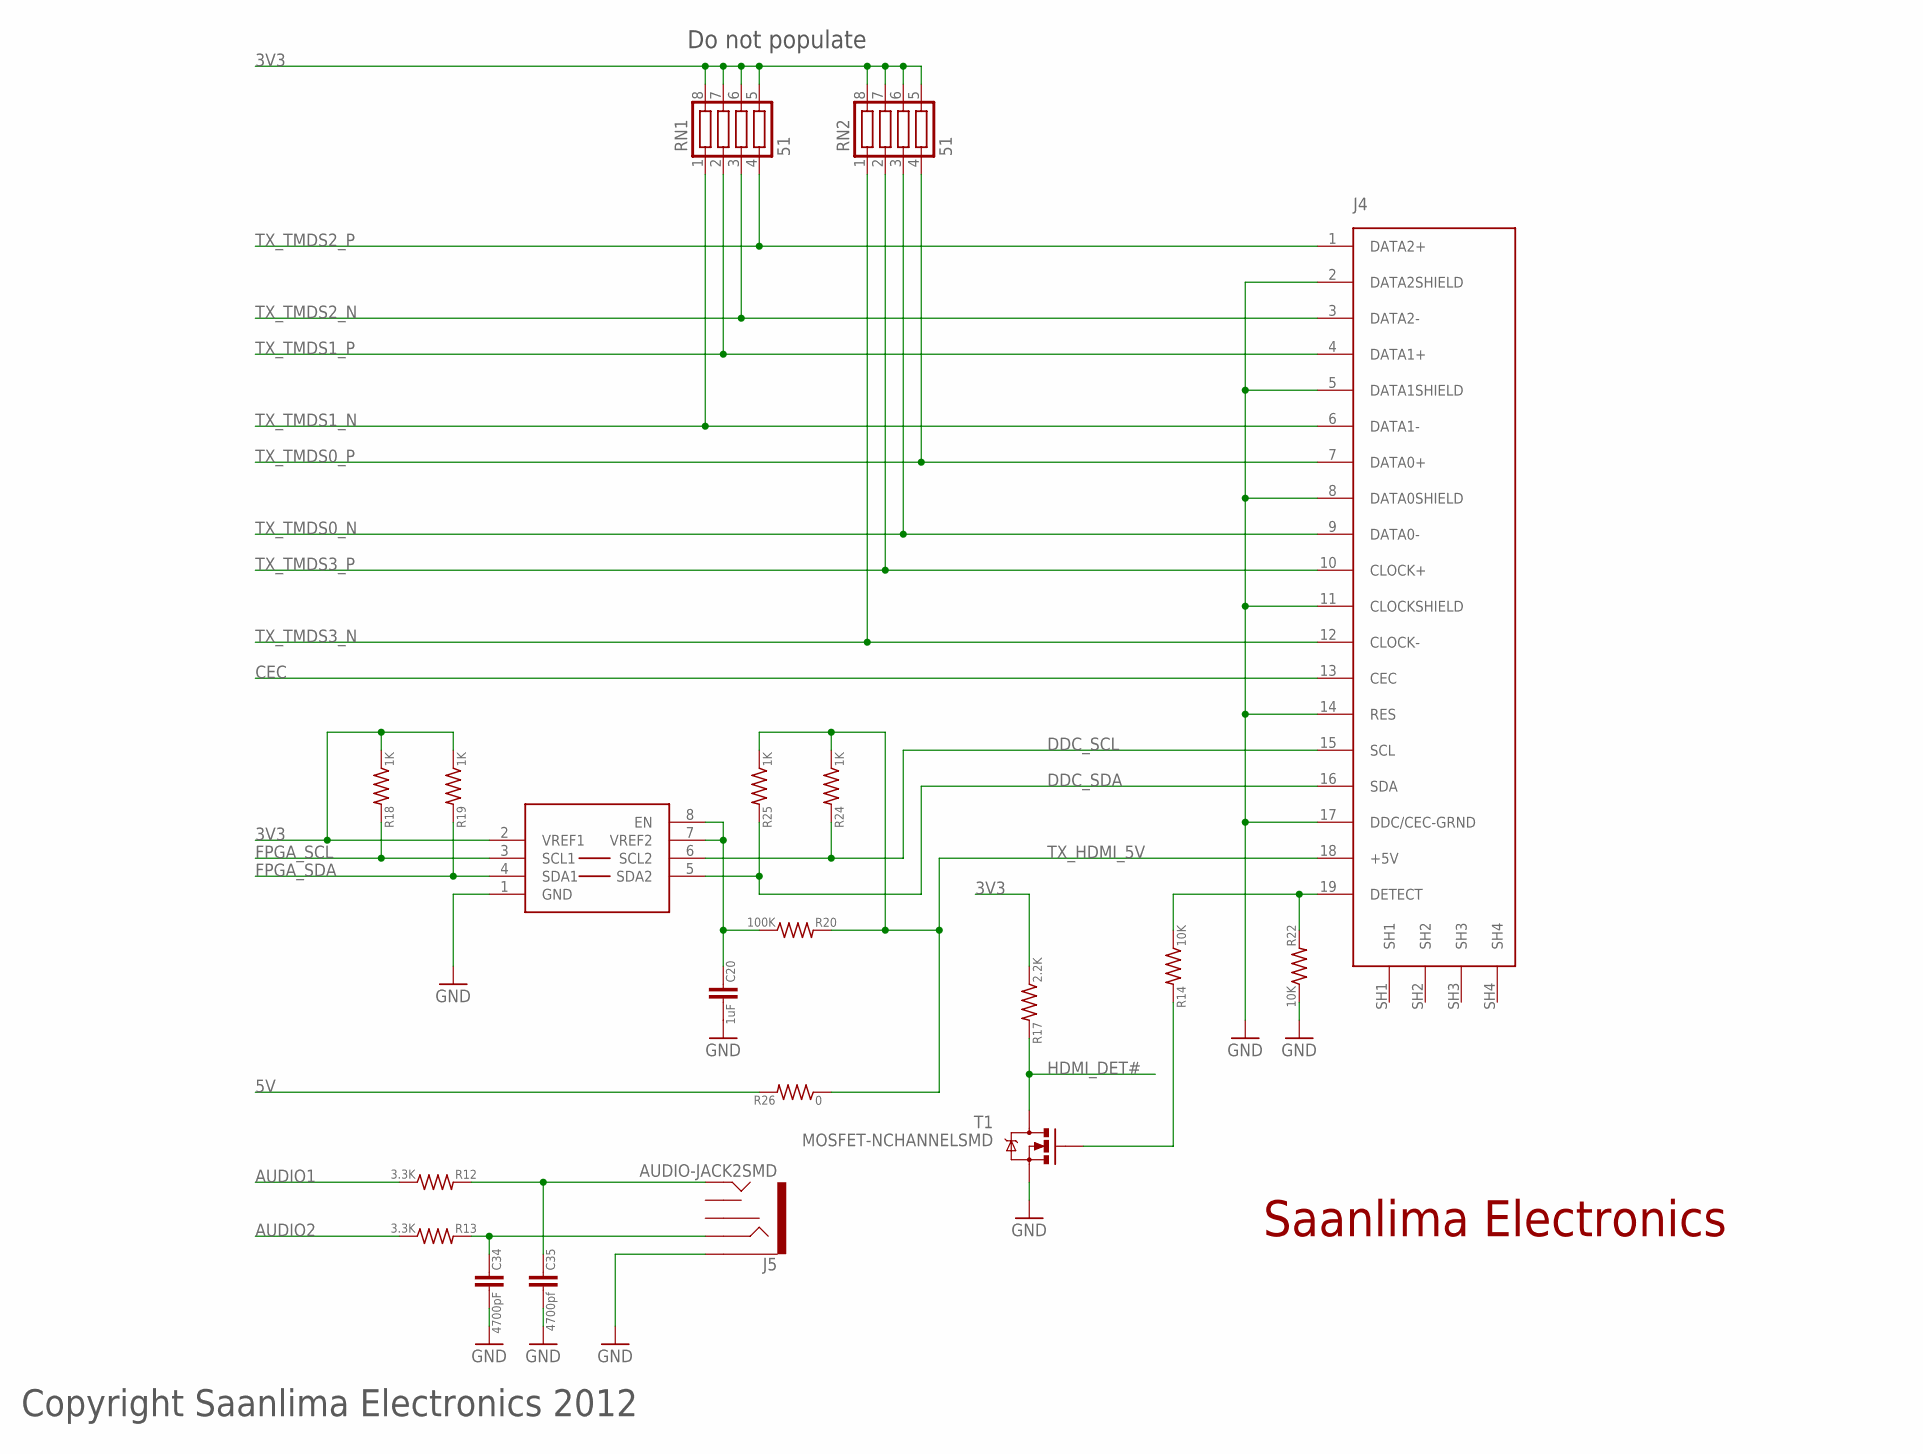
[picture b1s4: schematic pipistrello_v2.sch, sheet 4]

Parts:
C20: 1uF; 0402
C34: 4700pF; 0402
C35: 4700pf; 0402
J4: HDMI-TYPE-A-RECEPTICALFCI10029449; FCI-HDMI-TYPE-A-RECEPT
J5: AUDIO-JACK2SMD; AUDIO-JACK-3.5MM-SMD
R12, R13: 3.3K; 0402
R14, R22: 10K; 0402
R17: 2.2K; 0402
R18, R19, R24, R25: 1K; 0402
R20: 100K; 0402
R26: 0; 0402
RN1, RN2: 51; CTS742C083
T1: MOSFET-NCHANNELSMD; SOT23-3
U11: PCA9306; PSOP-8

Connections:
3V3: R17.1, R18.1, R19.1, RN1.5, RN1.6, RN1.7, RN1.8, RN2.5, RN2.6, RN2.7, RN2.8, U11.2 (VREF1); also elsewhere on the board
5V: R26.2; also elsewhere on the board
AUDIO1: R12.1; also elsewhere on the board
AUDIO2: R13.1; also elsewhere on the board
CEC: J4.13 (CEC)
DDC_SCL: J4.15 (SCL), R24.2, U11.6 (SCL2)
DDC_SDA: J4.16 (SDA), R25.2, U11.5 (SDA2)
DETECT: J4.19 (DETECT), R14.1, R22.2
FPGA_SCL: R18.2, U11.3 (SCL1); also elsewhere on the board
FPGA_SDA: R19.2, U11.4 (SDA1); also elsewhere on the board
GND: C20.2, C34.2, C35.2, J4.2 (DATA2SHIELD), J4.5 (DATA1SHIELD), J4.8 (DATA0SHIELD), J4.11 (CLOCKSHIELD), J4.14 (RES), J4.17 (DDC/CEC-GRND), J5.SLEEVE, R22.1, T1.2 (S), U11.1 (GND); also elsewhere on the board
HDMI_DET#: R17.2, T1.3 (D); also elsewhere on the board
unnamed: C20.1, R20.1, U11.7 (VREF2), U11.8 (EN)
unnamed: R14.2, T1.1 (G)
unnamed: C34.1, J5.RING, R13.2
unnamed: C35.1, J5.TIP, R12.2
TX_HDMI_5V: J4.18 (+5V), R20.2, R24.1, R25.1, R26.1
TX_TMDS0_N: J4.9 (DATA0-), RN2.3; also elsewhere on the board
TX_TMDS0_P: J4.7 (DATA0+), RN2.4; also elsewhere on the board
TX_TMDS1_N: J4.6 (DATA1-), RN1.1; also elsewhere on the board
TX_TMDS1_P: J4.4 (DATA1+), RN1.2; also elsewhere on the board
TX_TMDS2_N: J4.3 (DATA2-), RN1.3; also elsewhere on the board
TX_TMDS2_P: J4.1 (DATA2+), RN1.4; also elsewhere on the board
TX_TMDS3_N: J4.12 (CLOCK-), RN2.1; also elsewhere on the board
TX_TMDS3_P: J4.10 (CLOCK+), RN2.2; also elsewhere on the board

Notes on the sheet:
Saanlima Electronics
Copyright Saanlima Electronics 2012
Do not populate
